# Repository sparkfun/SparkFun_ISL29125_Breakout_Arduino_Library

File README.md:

SparkFun ISL29125 Breakout Arduino Library
==========================================

[   
*RGB Light Sensor Breakout-ISL29125 (SEN-12829)*](https://www.sparkfun.com/products/12829)

A Breakout Board and supporting code for the ISL29125 RGB Light Sensor.

Repository Contents
-------------------

* **/examples** - Example sketches for the library (.ino). Run these from the Arduino IDE. 
* **/src** - Source files for the library (.cpp, .h).
* **library.properties** - General library properties for the Arduino package manager. 

Documentation
--------------

* **[Hookup Guide](https://learn.sparkfun.com/tutorials/isl29125-rgb-light-sensor-hookup-guide?_ga=1.227771679.304927311.1426541708)** - Basic hookup guide for the SparkFun ISL29125 Breakout.
* **[Product Repository](https://github.com/sparkfun/ISL29125_Breakout)** - Main repository (including hardware files) for the SparkFun ISL29125 Breakout.

License Information
-------------------
The hardware is released under [Creative Commons ShareAlike 4.0 International](https://creativecommons.org/licenses/by-sa/4.0/).

Distributed as-is; no warranty is given.

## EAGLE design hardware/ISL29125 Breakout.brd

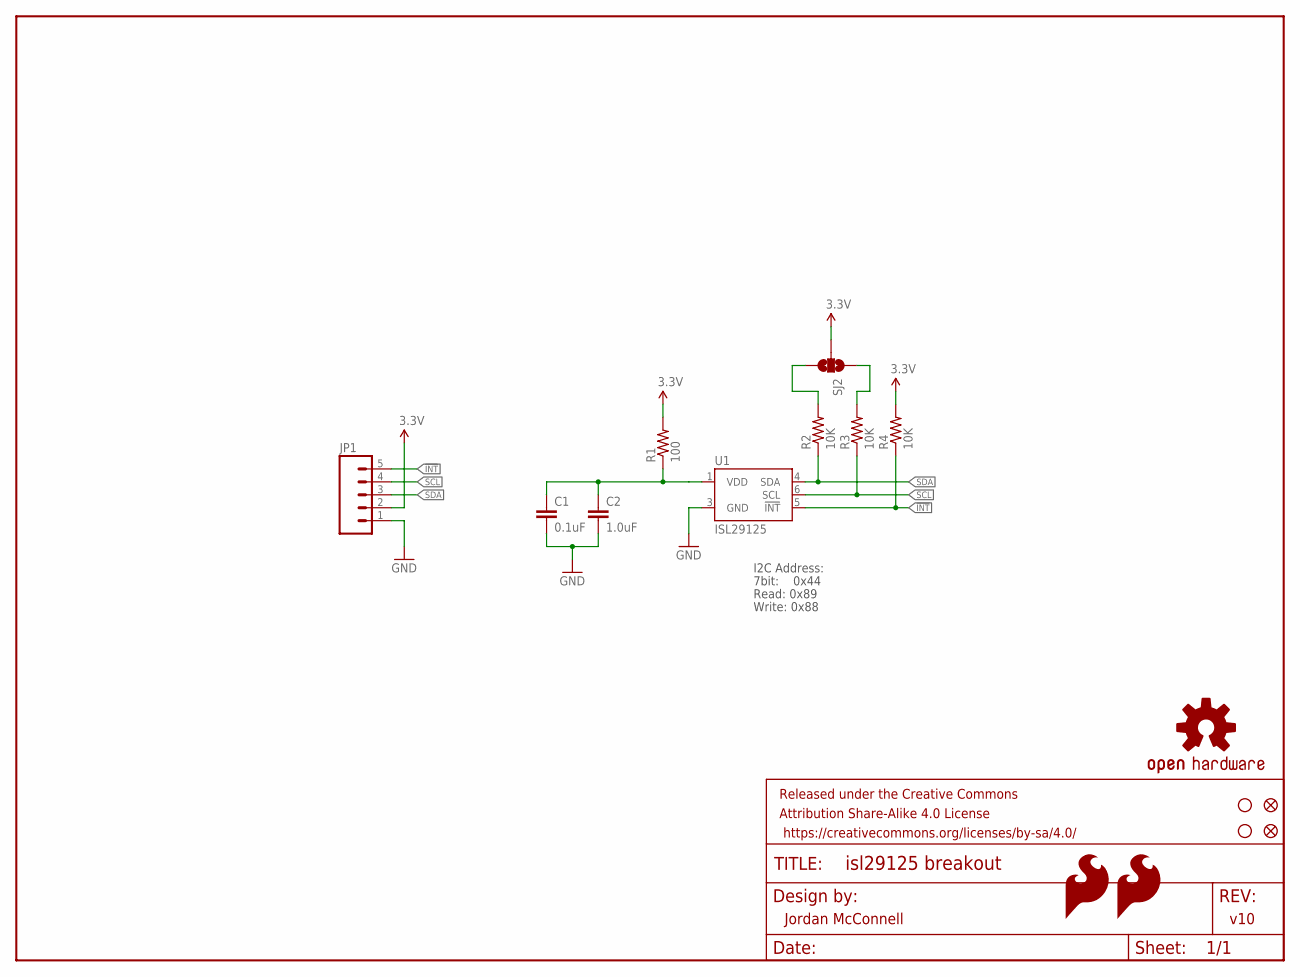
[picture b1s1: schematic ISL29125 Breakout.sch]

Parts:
C1: 0.1uF; 0603-CAP
C2: 1.0uF; 0603-CAP
FID1, FID2: FIDUCIAL1X2; FIDUCIAL-1X2
FRAME1: FRAME-LETTER; CREATIVE_COMMONS
JP1: M05PTH; 1X05
LOGO2, LOGO4: SFE_LOGO_FLAME.2_INCH; SFE_LOGO_FLAME_.2
LOGO3: OSHW-LOGOS; OSHW-LOGO-S
R1: 100; 0603-RES
R2, R3, R4: 10K; 0603-RES
SJ2: SOLDERJUMPER_2WAYS; SJ_3
STANDOFF1, STANDOFF2: STAND-OFF
U1: ISL29125; ODFN-LD-6

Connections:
3.3V: JP1.2, R1.2, R4.2, SJ2.2
!INT: JP1.5, R4.1, U1.5 (!INT)
GND: C1.2, C2.2, JP1.1, U1.3 (GND)
unnamed: C1.1, C2.1, R1.1, U1.1 (VDD)
unnamed: R2.2, SJ2.3
unnamed: R3.2, SJ2.1
SCL: JP1.4, R3.1, U1.6 (SCL)
SDA: JP1.3, R2.1, U1.4 (SDA)

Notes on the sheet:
Jordan McConnell
v10
7bit: 0x44
I2C Address:
Read: 0x89
Write: 0x88

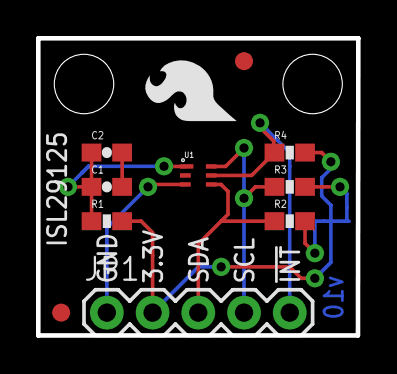
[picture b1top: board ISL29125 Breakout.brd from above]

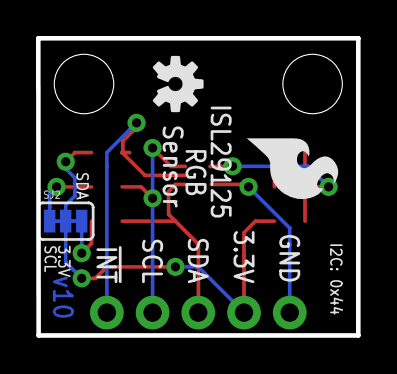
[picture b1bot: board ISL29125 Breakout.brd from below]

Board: 2 copper layers, 17.8 x 16.5 mm, 17 parts (3 on the bottom side), 8 nets.

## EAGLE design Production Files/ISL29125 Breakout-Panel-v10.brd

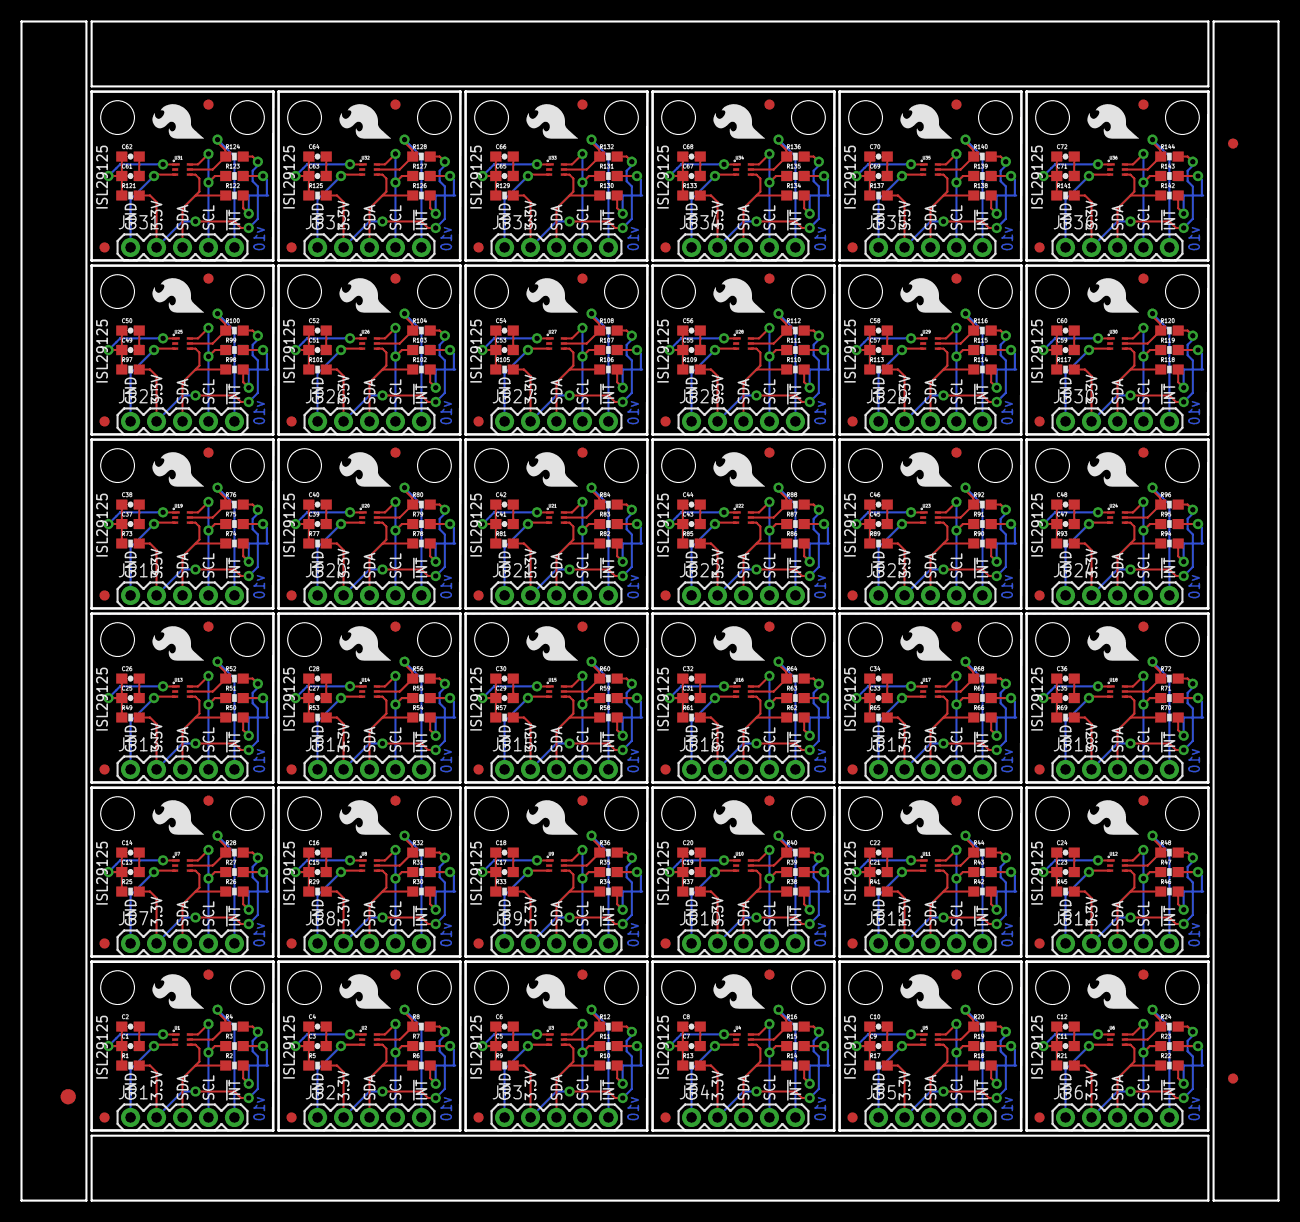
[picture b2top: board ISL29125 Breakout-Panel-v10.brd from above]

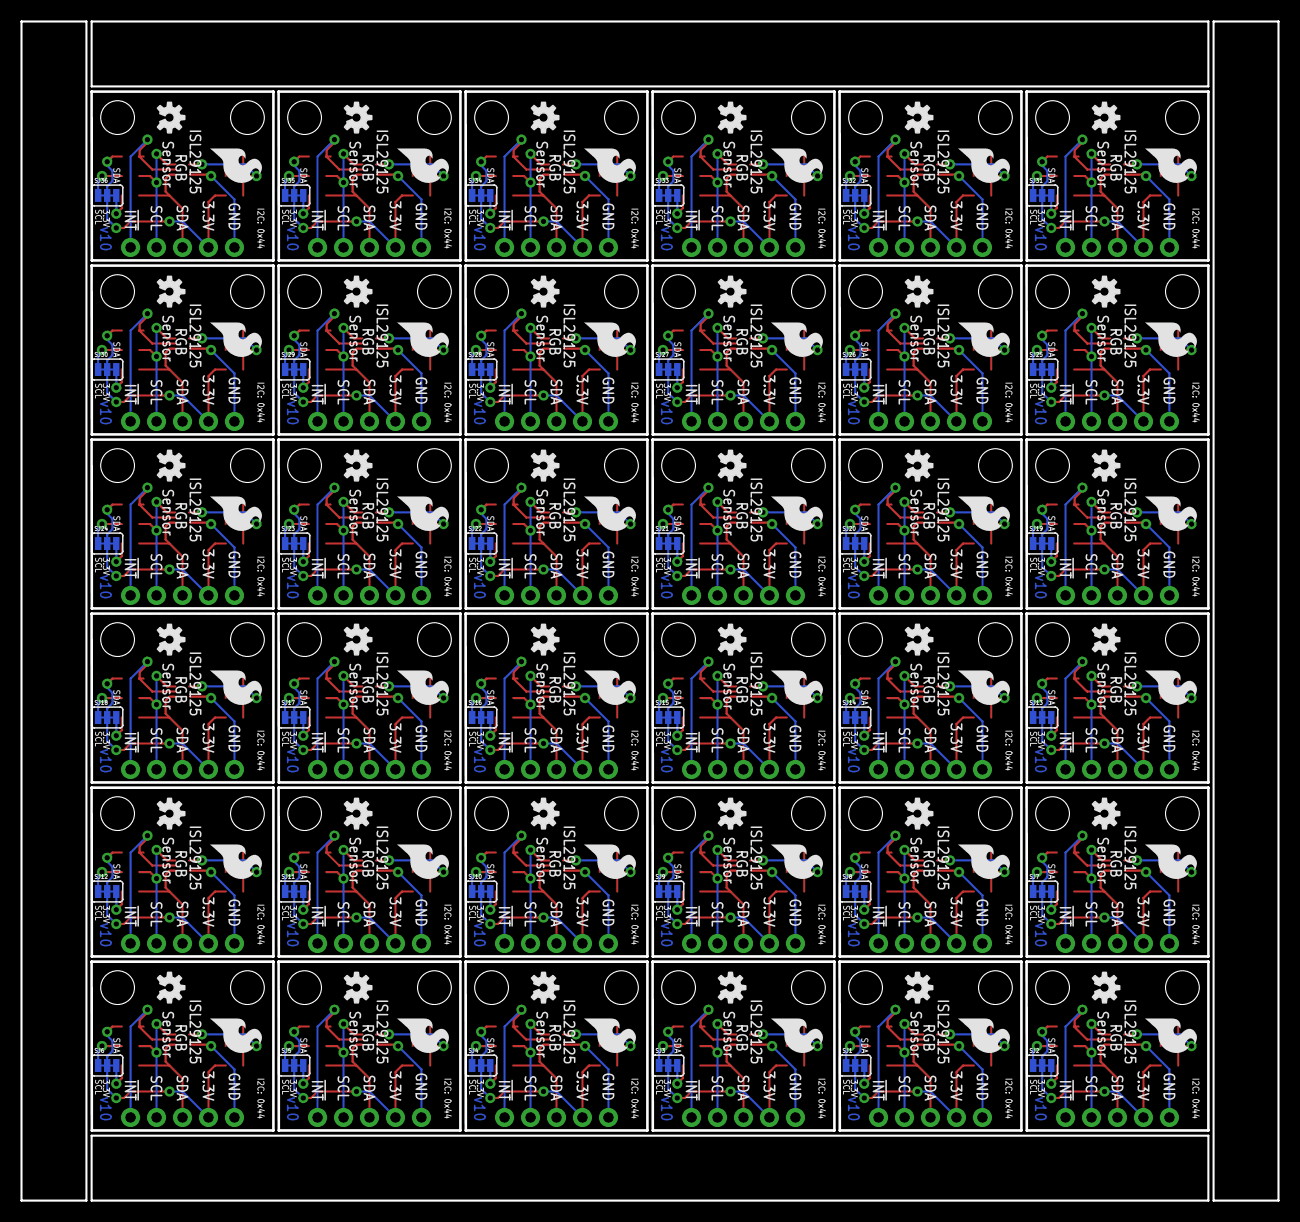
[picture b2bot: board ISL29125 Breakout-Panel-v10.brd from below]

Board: 2 copper layers, 122.9 x 115.3 mm, 579 parts (108 on the bottom side), 288 nets.

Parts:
C1, C3, C5, C7, C9, C11, C13, C15, C17, C19, C21, C23, C25, C27, C29, C31, C33, C35, C37, C39, C41, C43, C45, C47, C49, C51, C53, C55, C57, C59, C61, C63, C65, C67, C69, C71: 0.1uF; 0603-CAP
C2, C4, C6, C8, C10, C12, C14, C16, C18, C20, C22, C24, C26, C28, C30, C32, C34, C36, C38, C40, C42, C44, C46, C48, C50, C52, C54, C56, C58, C60, C62, C64, C66, C68, C70, C72: 1.0uF; 0603-CAP
E$1: FIDUCIAL-1.5X3
E$4, E$6: FIDUCIAL-1X2
FID1, FID2, FID3, FID4, FID5, FID6, FID7, FID8, FID9, FID10, FID11, FID12, FID13, FID14, FID15, FID16, FID17, FID18, FID19, FID20, FID21, FID22, FID23, FID24, FID25, FID26, FID27, FID28, FID29, FID30, FID31, FID32, FID33, FID34, FID35, FID36, FID37, FID38, FID39, FID40, FID41, FID42, FID43, FID44, FID45, FID46, FID47, FID48, FID49, FID50, FID51, FID52, FID53, FID54, FID55, FID56, FID57, FID58, FID59, FID60, FID61, FID62, FID63, FID64, FID65, FID66, FID67, FID68, FID69, FID70, FID71, FID72: FIDUCIAL1X2; FIDUCIAL-1X2
JP1, JP2, JP3, JP4, JP5, JP6, JP7, JP8, JP9, JP10, JP11, JP12, JP13, JP14, JP15, JP16, JP17, JP18, JP19, JP20, JP21, JP22, JP23, JP24, JP25, JP26, JP27, JP28, JP29, JP30, JP31, JP32, JP33, JP34, JP35, JP36: 1X05
LOGO1, LOGO3, LOGO7, LOGO10, LOGO13, LOGO16, LOGO19, LOGO22, LOGO25, LOGO28, LOGO31, LOGO34, LOGO37, LOGO40, LOGO43, LOGO46, LOGO49, LOGO52, LOGO55, LOGO58, LOGO61, LOGO64, LOGO67, LOGO70, LOGO73, LOGO76, LOGO79, LOGO82, LOGO85, LOGO88, LOGO91, LOGO94, LOGO97, LOGO100, LOGO103, LOGO106: OSHW-LOGOS; OSHW-LOGO-S
LOGO2, LOGO4, LOGO5, LOGO6, LOGO8, LOGO9, LOGO11, LOGO12, LOGO14, LOGO15, LOGO17, LOGO18, LOGO20, LOGO21, LOGO23, LOGO24, LOGO26, LOGO27, LOGO29, LOGO30, LOGO32, LOGO33, LOGO35, LOGO36, LOGO38, LOGO39, LOGO41, LOGO42, LOGO44, LOGO45, LOGO47, LOGO48, LOGO50, LOGO51, LOGO53, LOGO54, LOGO56, LOGO57, LOGO59, LOGO60, LOGO62, LOGO63, LOGO65, LOGO66, LOGO68, LOGO69, LOGO71, LOGO72, LOGO74, LOGO75, LOGO77, LOGO78, LOGO80, LOGO81, LOGO83, LOGO84, LOGO86, LOGO87, LOGO89, LOGO90, LOGO92, LOGO93, LOGO95, LOGO96, LOGO98, LOGO99, LOGO101, LOGO102, LOGO104, LOGO105, LOGO107, LOGO108: SFE_LOGO_FLAME.2_INCH; SFE_LOGO_FLAME_.2
R1, R5, R9, R13, R17, R21, R25, R29, R33, R37, R41, R45, R49, R53, R57, R61, R65, R69, R73, R77, R81, R85, R89, R93, R97, R101, R105, R109, R113, R117, R121, R125, R129, R133, R137, R141: 100; 0603-RES
R2, R3, R4, R6, R7, R8, R10, R11, R12, R14, R15, R16, R18, R19, R20, R22, R23, R24, R26, R27, R28, R30, R31, R32, R34, R35, R36, R38, R39, R40, R42, R43, R44, R46, R47, R48, R50, R51, R52, R54, R55, R56, R58, R59, R60, R62, R63, R64, R66, R67, R68, R70, R71, R72, R74, R75, R76, R78, R79, R80, R82, R83, R84, R86, R87, R88, R90, R91, R92, R94, R95, R96, R98, R99, R100, R102, R103, R104, R106, R107, R108, R110, R111, R112, R114, R115, R116, R118, R119, R120, R122, R123, R124, R126, R127, R128, R130, R131, R132, R134, R135, R136, R138, R139, R140, R142, R143, R144: 10K; 0603-RES
SJ1, SJ2, SJ3, SJ4, SJ5, SJ6, SJ7, SJ8, SJ9, SJ10, SJ11, SJ12, SJ13, SJ14, SJ15, SJ16, SJ17, SJ18, SJ19, SJ20, SJ21, SJ22, SJ23, SJ24, SJ25, SJ26, SJ27, SJ28, SJ29, SJ30, SJ31, SJ32, SJ33, SJ34, SJ35, SJ36: SJ_3
STANDOFF1, STANDOFF2, STANDOFF3, STANDOFF4, STANDOFF5, STANDOFF6, STANDOFF7, STANDOFF8, STANDOFF9, STANDOFF10, STANDOFF11, STANDOFF12, STANDOFF13, STANDOFF14, STANDOFF15, STANDOFF16, STANDOFF17, STANDOFF18, STANDOFF19, STANDOFF20, STANDOFF21, STANDOFF22, STANDOFF23, STANDOFF24, STANDOFF25, STANDOFF26, STANDOFF27, STANDOFF28, STANDOFF29, STANDOFF30, STANDOFF31, STANDOFF32, STANDOFF33, STANDOFF34, STANDOFF35, STANDOFF36, STANDOFF37, STANDOFF38, STANDOFF39, STANDOFF40, STANDOFF41, STANDOFF42, STANDOFF43, STANDOFF44, STANDOFF45, STANDOFF46, STANDOFF47, STANDOFF48, STANDOFF49, STANDOFF50, STANDOFF51, STANDOFF52, STANDOFF53, STANDOFF54, STANDOFF55, STANDOFF56, STANDOFF57, STANDOFF58, STANDOFF59, STANDOFF60, STANDOFF61, STANDOFF62, STANDOFF63, STANDOFF64, STANDOFF65, STANDOFF66, STANDOFF67, STANDOFF68, STANDOFF69, STANDOFF70, STANDOFF71, STANDOFF72: STAND-OFF
U1, U2, U3, U4, U5, U6, U7, U8, U9, U10, U11, U12, U13, U14, U15, U16, U17, U18, U19, U20, U21, U22, U23, U24, U25, U26, U27, U28, U29, U30, U31, U32, U33, U34, U35, U36: ISL29125; ODFN-LD-6

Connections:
3.3V: JP1.2, R1.2, R4.2, SJ2.2
3.3V1: JP2.2, R5.2, R8.2, SJ1.2
3.3V2: JP3.2, R9.2, R12.2, SJ3.2
3.3V3: JP4.2, R13.2, R16.2, SJ4.2
3.3V4: JP5.2, R17.2, R20.2, SJ5.2
3.3V5: JP6.2, R21.2, R24.2, SJ6.2
3.3V6: JP7.2, R25.2, R28.2, SJ7.2
3.3V7: JP8.2, R29.2, R32.2, SJ8.2
3.3V8: JP9.2, R33.2, R36.2, SJ9.2
3.3V9: JP10.2, R37.2, R40.2, SJ10.2
3.3V10: JP11.2, R41.2, R44.2, SJ11.2
3.3V11: JP12.2, R45.2, R48.2, SJ12.2
3.3V12: JP13.2, R49.2, R52.2, SJ13.2
3.3V13: JP14.2, R53.2, R56.2, SJ14.2
3.3V14: JP15.2, R57.2, R60.2, SJ15.2
3.3V15: JP16.2, R61.2, R64.2, SJ16.2
3.3V16: JP17.2, R65.2, R68.2, SJ17.2
3.3V17: JP18.2, R69.2, R72.2, SJ18.2
3.3V18: JP19.2, R73.2, R76.2, SJ19.2
3.3V19: JP20.2, R77.2, R80.2, SJ20.2
3.3V20: JP21.2, R81.2, R84.2, SJ21.2
3.3V21: JP22.2, R85.2, R88.2, SJ22.2
3.3V22: JP23.2, R89.2, R92.2, SJ23.2
3.3V23: JP24.2, R93.2, R96.2, SJ24.2
3.3V24: JP25.2, R97.2, R100.2, SJ25.2
3.3V25: JP26.2, R101.2, R104.2, SJ26.2
3.3V26: JP27.2, R105.2, R108.2, SJ27.2
3.3V27: JP28.2, R109.2, R112.2, SJ28.2
3.3V28: JP29.2, R113.2, R116.2, SJ29.2
3.3V29: JP30.2, R117.2, R120.2, SJ30.2
3.3V30: JP31.2, R121.2, R124.2, SJ31.2
3.3V31: JP32.2, R125.2, R128.2, SJ32.2
3.3V32: JP33.2, R129.2, R132.2, SJ33.2
3.3V33: JP34.2, R133.2, R136.2, SJ34.2
3.3V34: JP35.2, R137.2, R140.2, SJ35.2
3.3V35: JP36.2, R141.2, R144.2, SJ36.2
!INT: JP1.5, R4.1, U1.5
!INT1: JP2.5, R8.1, U2.5
!INT2: JP3.5, R12.1, U3.5
!INT3: JP4.5, R16.1, U4.5
!INT4: JP5.5, R20.1, U5.5
!INT5: JP6.5, R24.1, U6.5
!INT6: JP7.5, R28.1, U7.5
!INT7: JP8.5, R32.1, U8.5
!INT8: JP9.5, R36.1, U9.5
!INT9: JP10.5, R40.1, U10.5
!INT10: JP11.5, R44.1, U11.5
!INT11: JP12.5, R48.1, U12.5
!INT12: JP13.5, R52.1, U13.5
!INT13: JP14.5, R56.1, U14.5
!INT14: JP15.5, R60.1, U15.5
!INT15: JP16.5, R64.1, U16.5
!INT16: JP17.5, R68.1, U17.5
!INT17: JP18.5, R72.1, U18.5
!INT18: JP19.5, R76.1, U19.5
!INT19: JP20.5, R80.1, U20.5
!INT20: JP21.5, R84.1, U21.5
!INT21: JP22.5, R88.1, U22.5
!INT22: JP23.5, R92.1, U23.5
!INT23: JP24.5, R96.1, U24.5
!INT24: JP25.5, R100.1, U25.5
!INT25: JP26.5, R104.1, U26.5
!INT26: JP27.5, R108.1, U27.5
!INT27: JP28.5, R112.1, U28.5
!INT28: JP29.5, R116.1, U29.5
!INT29: JP30.5, R120.1, U30.5
!INT30: JP31.5, R124.1, U31.5
!INT31: JP32.5, R128.1, U32.5
!INT32: JP33.5, R132.1, U33.5
!INT33: JP34.5, R136.1, U34.5
!INT34: JP35.5, R140.1, U35.5
!INT35: JP36.5, R144.1, U36.5
GND: C1.2, C2.2, JP1.1, U1.3
GND1: C3.2, C4.2, JP2.1, U2.3
GND2: C5.2, C6.2, JP3.1, U3.3
GND3: C7.2, C8.2, JP4.1, U4.3
GND4: C9.2, C10.2, JP5.1, U5.3
GND5: C11.2, C12.2, JP6.1, U6.3
GND6: C13.2, C14.2, JP7.1, U7.3
GND7: C15.2, C16.2, JP8.1, U8.3
GND8: C17.2, C18.2, JP9.1, U9.3
GND9: C19.2, C20.2, JP10.1, U10.3
GND10: C21.2, C22.2, JP11.1, U11.3
GND11: C23.2, C24.2, JP12.1, U12.3
GND12: C25.2, C26.2, JP13.1, U13.3
GND13: C27.2, C28.2, JP14.1, U14.3
GND14: C29.2, C30.2, JP15.1, U15.3
GND15: C31.2, C32.2, JP16.1, U16.3
GND16: C33.2, C34.2, JP17.1, U17.3
GND17: C35.2, C36.2, JP18.1, U18.3
GND18: C37.2, C38.2, JP19.1, U19.3
GND19: C39.2, C40.2, JP20.1, U20.3
GND20: C41.2, C42.2, JP21.1, U21.3
GND21: C43.2, C44.2, JP22.1, U22.3
GND22: C45.2, C46.2, JP23.1, U23.3
GND23: C47.2, C48.2, JP24.1, U24.3
GND24: C49.2, C50.2, JP25.1, U25.3
GND25: C51.2, C52.2, JP26.1, U26.3
GND26: C53.2, C54.2, JP27.1, U27.3
GND27: C55.2, C56.2, JP28.1, U28.3
GND28: C57.2, C58.2, JP29.1, U29.3
GND29: C59.2, C60.2, JP30.1, U30.3
GND30: C61.2, C62.2, JP31.1, U31.3
GND31: C63.2, C64.2, JP32.1, U32.3
GND32: C65.2, C66.2, JP33.1, U33.3
GND33: C67.2, C68.2, JP34.1, U34.3
GND34: C69.2, C70.2, JP35.1, U35.3
GND35: C71.2, C72.2, JP36.1, U36.3
unnamed: C1.1, C2.1, R1.1, U1.1
unnamed: C3.1, C4.1, R5.1, U2.1
unnamed: R2.2, SJ2.3
unnamed: R3.2, SJ2.1
unnamed: R6.2, SJ1.3
unnamed: R7.2, SJ1.1
unnamed: C5.1, C6.1, R9.1, U3.1
unnamed: R10.2, SJ3.3
unnamed: R11.2, SJ3.1
unnamed: C7.1, C8.1, R13.1, U4.1
unnamed: R14.2, SJ4.3
unnamed: R15.2, SJ4.1
unnamed: C9.1, C10.1, R17.1, U5.1
unnamed: R18.2, SJ5.3
unnamed: R19.2, SJ5.1
unnamed: C11.1, C12.1, R21.1, U6.1
unnamed: R22.2, SJ6.3
unnamed: R23.2, SJ6.1
unnamed: C13.1, C14.1, R25.1, U7.1
unnamed: R26.2, SJ7.3
unnamed: R27.2, SJ7.1
unnamed: C15.1, C16.1, R29.1, U8.1
unnamed: R30.2, SJ8.3
unnamed: R31.2, SJ8.1
unnamed: C17.1, C18.1, R33.1, U9.1
unnamed: R34.2, SJ9.3
unnamed: R35.2, SJ9.1
unnamed: C19.1, C20.1, R37.1, U10.1
unnamed: R38.2, SJ10.3
unnamed: R39.2, SJ10.1
unnamed: C21.1, C22.1, R41.1, U11.1
unnamed: R42.2, SJ11.3
unnamed: R43.2, SJ11.1
unnamed: C23.1, C24.1, R45.1, U12.1
unnamed: R46.2, SJ12.3
unnamed: R47.2, SJ12.1
unnamed: C25.1, C26.1, R49.1, U13.1
unnamed: R50.2, SJ13.3
unnamed: R51.2, SJ13.1
unnamed: C27.1, C28.1, R53.1, U14.1
unnamed: R54.2, SJ14.3
unnamed: R55.2, SJ14.1
unnamed: C29.1, C30.1, R57.1, U15.1
unnamed: R58.2, SJ15.3
unnamed: R59.2, SJ15.1
unnamed: C31.1, C32.1, R61.1, U16.1
unnamed: R62.2, SJ16.3
unnamed: R63.2, SJ16.1
unnamed: C33.1, C34.1, R65.1, U17.1
unnamed: R66.2, SJ17.3
unnamed: R67.2, SJ17.1
unnamed: C35.1, C36.1, R69.1, U18.1
unnamed: R70.2, SJ18.3
unnamed: R71.2, SJ18.1
unnamed: C37.1, C38.1, R73.1, U19.1
unnamed: R74.2, SJ19.3
unnamed: R75.2, SJ19.1
unnamed: C39.1, C40.1, R77.1, U20.1
unnamed: R78.2, SJ20.3
unnamed: R79.2, SJ20.1
unnamed: C41.1, C42.1, R81.1, U21.1
unnamed: R82.2, SJ21.3
unnamed: R83.2, SJ21.1
unnamed: C43.1, C44.1, R85.1, U22.1
unnamed: R86.2, SJ22.3
unnamed: R87.2, SJ22.1
unnamed: C45.1, C46.1, R89.1, U23.1
unnamed: R90.2, SJ23.3
unnamed: R91.2, SJ23.1
unnamed: C47.1, C48.1, R93.1, U24.1
unnamed: R94.2, SJ24.3
unnamed: R95.2, SJ24.1
unnamed: C49.1, C50.1, R97.1, U25.1
unnamed: R98.2, SJ25.3
unnamed: R99.2, SJ25.1
unnamed: C51.1, C52.1, R101.1, U26.1
unnamed: R102.2, SJ26.3
unnamed: R103.2, SJ26.1
unnamed: C53.1, C54.1, R105.1, U27.1
unnamed: R106.2, SJ27.3
unnamed: R107.2, SJ27.1
unnamed: C55.1, C56.1, R109.1, U28.1
unnamed: R110.2, SJ28.3
unnamed: R111.2, SJ28.1
unnamed: C57.1, C58.1, R113.1, U29.1
unnamed: R114.2, SJ29.3
unnamed: R115.2, SJ29.1
unnamed: C59.1, C60.1, R117.1, U30.1
unnamed: R118.2, SJ30.3
unnamed: R119.2, SJ30.1
unnamed: C61.1, C62.1, R121.1, U31.1
unnamed: R122.2, SJ31.3
unnamed: R123.2, SJ31.1
unnamed: C63.1, C64.1, R125.1, U32.1
unnamed: R126.2, SJ32.3
unnamed: R127.2, SJ32.1
unnamed: C65.1, C66.1, R129.1, U33.1
unnamed: R130.2, SJ33.3
unnamed: R131.2, SJ33.1
unnamed: C67.1, C68.1, R133.1, U34.1
unnamed: R134.2, SJ34.3
unnamed: R135.2, SJ34.1
unnamed: C69.1, C70.1, R137.1, U35.1
unnamed: R138.2, SJ35.3
unnamed: R139.2, SJ35.1
unnamed: C71.1, C72.1, R141.1, U36.1
unnamed: R142.2, SJ36.3
unnamed: R143.2, SJ36.1
SCL: JP1.4, R3.1, U1.6
SCL1: JP2.4, R7.1, U2.6
SCL2: JP3.4, R11.1, U3.6
SCL3: JP4.4, R15.1, U4.6
SCL4: JP5.4, R19.1, U5.6
SCL5: JP6.4, R23.1, U6.6
SCL6: JP7.4, R27.1, U7.6
SCL7: JP8.4, R31.1, U8.6
SCL8: JP9.4, R35.1, U9.6
SCL9: JP10.4, R39.1, U10.6
SCL10: JP11.4, R43.1, U11.6
SCL11: JP12.4, R47.1, U12.6
SCL12: JP13.4, R51.1, U13.6
SCL13: JP14.4, R55.1, U14.6
SCL14: JP15.4, R59.1, U15.6
SCL15: JP16.4, R63.1, U16.6
SCL16: JP17.4, R67.1, U17.6
SCL17: JP18.4, R71.1, U18.6
SCL18: JP19.4, R75.1, U19.6
SCL19: JP20.4, R79.1, U20.6
SCL20: JP21.4, R83.1, U21.6
SCL21: JP22.4, R87.1, U22.6
SCL22: JP23.4, R91.1, U23.6
SCL23: JP24.4, R95.1, U24.6
SCL24: JP25.4, R99.1, U25.6
SCL25: JP26.4, R103.1, U26.6
SCL26: JP27.4, R107.1, U27.6
SCL27: JP28.4, R111.1, U28.6
SCL28: JP29.4, R115.1, U29.6
SCL29: JP30.4, R119.1, U30.6
SCL30: JP31.4, R123.1, U31.6
SCL31: JP32.4, R127.1, U32.6
SCL32: JP33.4, R131.1, U33.6
SCL33: JP34.4, R135.1, U34.6
SCL34: JP35.4, R139.1, U35.6
SCL35: JP36.4, R143.1, U36.6
SDA: JP1.3, R2.1, U1.4
SDA1: JP2.3, R6.1, U2.4
SDA2: JP3.3, R10.1, U3.4
SDA3: JP4.3, R14.1, U4.4
SDA4: JP5.3, R18.1, U5.4
SDA5: JP6.3, R22.1, U6.4
SDA6: JP7.3, R26.1, U7.4
SDA7: JP8.3, R30.1, U8.4
SDA8: JP9.3, R34.1, U9.4
SDA9: JP10.3, R38.1, U10.4
SDA10: JP11.3, R42.1, U11.4
SDA11: JP12.3, R46.1, U12.4
SDA12: JP13.3, R50.1, U13.4
SDA13: JP14.3, R54.1, U14.4
SDA14: JP15.3, R58.1, U15.4
SDA15: JP16.3, R62.1, U16.4
SDA16: JP17.3, R66.1, U17.4
SDA17: JP18.3, R70.1, U18.4
SDA18: JP19.3, R74.1, U19.4
SDA19: JP20.3, R78.1, U20.4
SDA20: JP21.3, R82.1, U21.4
SDA21: JP22.3, R86.1, U22.4
SDA22: JP23.3, R90.1, U23.4
SDA23: JP24.3, R94.1, U24.4
SDA24: JP25.3, R98.1, U25.4
SDA25: JP26.3, R102.1, U26.4
SDA26: JP27.3, R106.1, U27.4
SDA27: JP28.3, R110.1, U28.4
SDA28: JP29.3, R114.1, U29.4
SDA29: JP30.3, R118.1, U30.4
SDA30: JP31.3, R122.1, U31.4
SDA31: JP32.3, R126.1, U32.4
SDA32: JP33.3, R130.1, U33.4
SDA33: JP34.3, R134.1, U34.4
SDA34: JP35.3, R138.1, U35.4
SDA35: JP36.3, R142.1, U36.4

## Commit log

2014-03-14 v01 ready for protos
2014-03-19 v01, revised after review, ready for protos
2014-04-11 Initial library commit with two core examples
2014-04-18 Added configuration comments to library .h file
2014-04-18 Added interrupt driven example for the sensor
2014-04-18 hardware ready for reds, v10
2014-04-22 created panel v10
2014-04-30 updated basic example to explain sensor readings are 16bit uints
2014-06-11 Updated readme with product id and photo
2014-06-11 Slight readme adjustment
2015-04-24 Adding library structure for Arduino
2015-04-24 Updating README
2015-05-13 Fixing typos
2015-05-13 Fixing library.properties file
2019-09-06 Add contrubting and issue templates
2019-11-06 Remove unnecessary calls to beginTransmission and endTransmission
    Remove unnecessary calls to begin and end transmission.

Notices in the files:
parts and their libraries:
SparkFun-Aesthetics: Licensing: Creative Commons ShareAlike 4.0 International - https://creativecommons.org/licenses/by-sa/4.0
SparkFun-Aesthetics: Released under the Creative Commons Attribution Share-Alike 4.0 License
SparkFun-Aesthetics: Released under the Creative Commons
